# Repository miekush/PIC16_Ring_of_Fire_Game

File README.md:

# PIC16_Ring_of_Fire_Game
A PIC16 based LED Reaction Time Game

This is a simple LED reaction time game based on the classes light ring redemption games seen in arcades. 

# Project Description

The device uses a PIC16F15223 8-bit microcontroller to drive a ring of 1206 LEDs. A low cost tactile switch starts and stops the led chaser and allows for switching between game mode and a speed settings mode depending on the press duration. Programming the device is completed via the onboard Tag-Connect footprint.

# Breadboard Prototype

# Enclosure

To make the device more comfortable for handheld use, I designed a small enclosure which can be easily 3D printed for a more professional device appearence.

Designed by Mike Kushnerik (MKE) in KiCad V5

# License

MKE supports the open source hardware community by sharing hardware design files freely on GitHub!

Please support MKE by purchasing products on [Tindie](https://www.tindie.com/stores/mkengineering/)!

Designed by Mike Kushnerik for MKEngineering

Licensed under [Creative Commons Attribution-ShareAlike CC BY-SA 3.0](http://creativecommons.org/licenses/by-sa/3.0/)

All text above must be included in any redistribution!

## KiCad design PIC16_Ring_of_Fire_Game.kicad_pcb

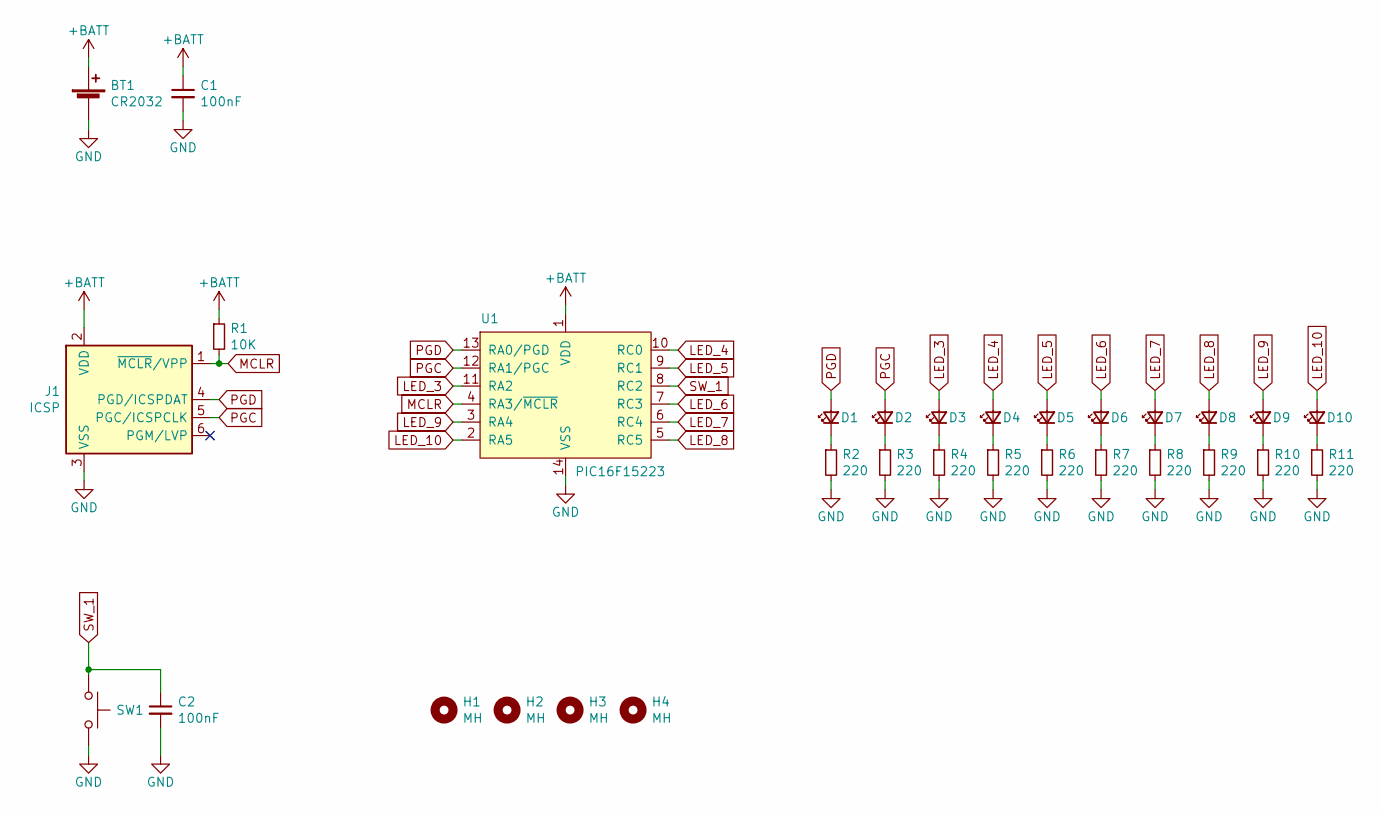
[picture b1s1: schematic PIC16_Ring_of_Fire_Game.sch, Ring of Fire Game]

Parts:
BT1: CR2032; 1060TR
C1, C2: 100nF; C_0603_1608Metric
D1, D2, D3, D4, D5, D6, D7, D8, D9, D10: 5mm LED; LED_1206_3216Metric
H1, H2, H3, H4: MH; MountingHole_3.2mm_M3
J1: ICSP; Tag-Connect_TC2030-IDC-NL_2x03_P1.27mm_Vertical
R1: 10K; R_0603_1608Metric
R2, R3, R4, R5, R6, R7, R8, R9, R10, R11: 220; R_0603_1608Metric
SW1: START/STOP; SW_SPST_PTS645
U1: PIC16F15223; SOIC-14_3.9x8.7mm_P1.27mm

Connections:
+BATT: BT1.1 (+), C1.1, J1.2 (VDD), R1.1, U1.1 (VDD)
GND: BT1.2 (-), C1.2, C2.2, J1.3 (VSS), R2.2, R3.2, R4.2, R5.2, R6.2, R7.2, R8.2, R9.2, R10.2, R11.2, SW1.1, U1.14 (VSS)
LED_3: D3.2 (A), U1.11 (RA2)
LED_4: D4.2 (A), U1.10 (RC0)
LED_5: D5.2 (A), U1.9 (RC1)
LED_6: D6.2 (A), U1.7 (RC3)
LED_7: D7.2 (A), U1.6 (RC4)
LED_8: D8.2 (A), U1.5 (RC5)
LED_9: D9.2 (A), U1.3 (RA4)
LED_10: D10.2 (A), U1.2 (RA5)
MCLR: J1.1 (~MCLR~/VPP), R1.2, U1.4 (RA3/~MCLR)
unnamed: D1.1 (K), R2.1
unnamed: D2.1 (K), R3.1
unnamed: D3.1 (K), R4.1
unnamed: D4.1 (K), R5.1
unnamed: D5.1 (K), R6.1
unnamed: D6.1 (K), R7.1
unnamed: D7.1 (K), R8.1
unnamed: D8.1 (K), R9.1
unnamed: D9.1 (K), R10.1
unnamed: D10.1 (K), R11.1
PGC: D2.2 (A), J1.5 (PGC/ICSPCLK), U1.12 (RA1/PGC)
PGD: D1.2 (A), J1.4 (PGD/ICSPDAT), U1.13 (RA0/PGD)
SW_1: C2.1, SW1.2, U1.8 (RC2)

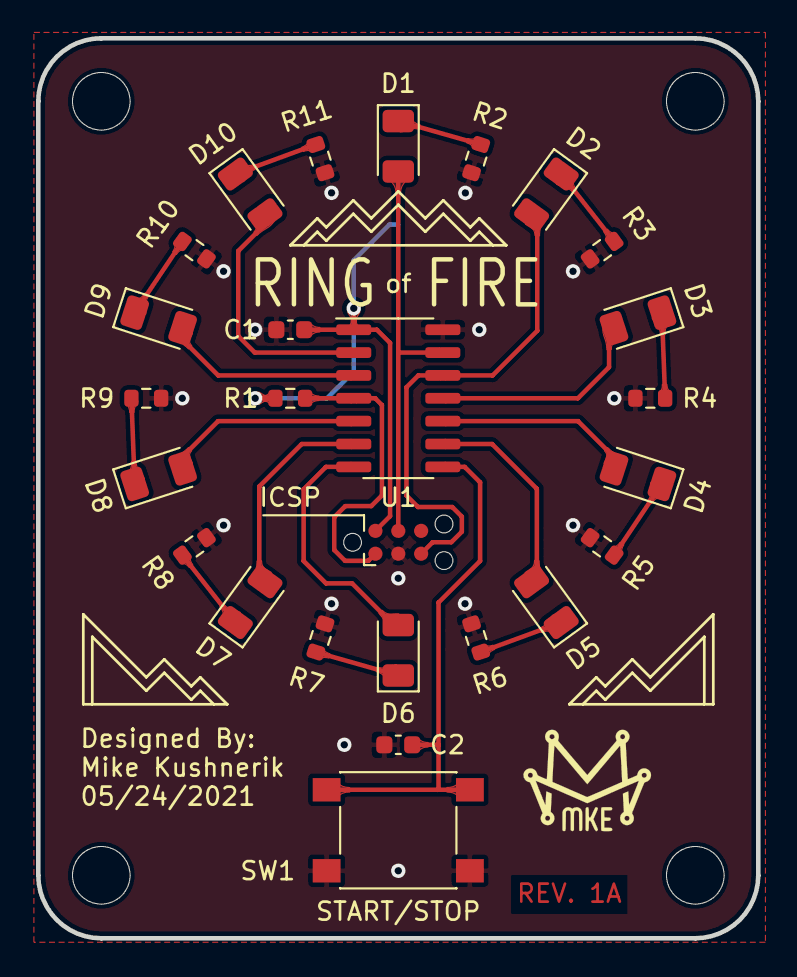
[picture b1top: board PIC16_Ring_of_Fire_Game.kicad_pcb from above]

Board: 2 copper layers, 40.0 x 50.0 mm, 31 parts (1 on the bottom side), 24 nets.

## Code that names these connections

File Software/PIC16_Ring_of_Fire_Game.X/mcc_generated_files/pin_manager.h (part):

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// get/set LED_1 aliases
#define LED_1_TRIS                 TRISAbits.TRISA0
#define LED_1_LAT                  LATAbits.LATA0
#define LED_1_PORT                 PORTAbits.RA0
#define LED_1_WPU                  WPUAbits.WPUA0
#define LED_1_OD                   ODCONAbits.ODCA0
#define LED_1_ANS                  ANSELAbits.ANSA0
#define LED_1_SetHigh()            do { LATAbits.LATA0 = 1; } while(0)
#define LED_1_SetLow()             do { LATAbits.LATA0 = 0; } while(0)
#define LED_1_Toggle()             do { LATAbits.LATA0 = ~LATAbits.LATA0; } while(0)
#define LED_1_GetValue()           PORTAbits.RA0
#define LED_1_SetDigitalInput()    do { TRISAbits.TRISA0 = 1; } while(0)
#define LED_1_SetDigitalOutput()   do { TRISAbits.TRISA0 = 0; } while(0)
#define LED_1_SetPullup()          do { WPUAbits.WPUA0 = 1; } while(0)
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// get/set LED_2 aliases
#define LED_2_TRIS                 TRISAbits.TRISA1
#define LED_2_LAT                  LATAbits.LATA1
#define LED_2_PORT                 PORTAbits.RA1
#define LED_2_WPU                  WPUAbits.WPUA1
#define LED_2_OD                   ODCONAbits.ODCA1
#define LED_2_ANS                  ANSELAbits.ANSA1
#define LED_2_SetHigh()            do { LATAbits.LATA1 = 1; } while(0)
#define LED_2_SetLow()             do { LATAbits.LATA1 = 0; } while(0)
#define LED_2_Toggle()             do { LATAbits.LATA1 = ~LATAbits.LATA1; } while(0)
#define LED_2_GetValue()           PORTAbits.RA1
#define LED_2_SetDigitalInput()    do { TRISAbits.TRISA1 = 1; } while(0)
#define LED_2_SetDigitalOutput()   do { TRISAbits.TRISA1 = 0; } while(0)
#define LED_2_SetPullup()          do { WPUAbits.WPUA1 = 1; } while(0)
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// get/set LED_3 aliases
#define LED_3_TRIS                 TRISAbits.TRISA2
#define LED_3_LAT                  LATAbits.LATA2
#define LED_3_PORT                 PORTAbits.RA2
#define LED_3_WPU                  WPUAbits.WPUA2
#define LED_3_OD                   ODCONAbits.ODCA2
#define LED_3_ANS                  ANSELAbits.ANSA2
#define LED_3_SetHigh()            do { LATAbits.LATA2 = 1; } while(0)
#define LED_3_SetLow()             do { LATAbits.LATA2 = 0; } while(0)
#define LED_3_Toggle()             do { LATAbits.LATA2 = ~LATAbits.LATA2; } while(0)
#define LED_3_GetValue()           PORTAbits.RA2
#define LED_3_SetDigitalInput()    do { TRISAbits.TRISA2 = 1; } while(0)
#define LED_3_SetDigitalOutput()   do { TRISAbits.TRISA2 = 0; } while(0)
#define LED_3_SetPullup()          do { WPUAbits.WPUA2 = 1; } while(0)
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// get/set LED_10 aliases
#define LED_10_TRIS                 TRISAbits.TRISA4
#define LED_10_LAT                  LATAbits.LATA4
#define LED_10_PORT                 PORTAbits.RA4
#define LED_10_WPU                  WPUAbits.WPUA4
#define LED_10_OD                   ODCONAbits.ODCA4
#define LED_10_ANS                  ANSELAbits.ANSA4
#define LED_10_SetHigh()            do { LATAbits.LATA4 = 1; } while(0)
#define LED_10_SetLow()             do { LATAbits.LATA4 = 0; } while(0)
#define LED_10_Toggle()             do { LATAbits.LATA4 = ~LATAbits.LATA4; } while(0)
#define LED_10_GetValue()           PORTAbits.RA4
#define LED_10_SetDigitalInput()    do { TRISAbits.TRISA4 = 1; } while(0)
#define LED_10_SetDigitalOutput()   do { TRISAbits.TRISA4 = 0; } while(0)
#define LED_10_SetPullup()          do { WPUAbits.WPUA4 = 1; } while(0)
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#define RA5_SetHigh()            do { LATAbits.LATA5 = 1; } while(0)
#define RA5_SetLow()             do { LATAbits.LATA5 = 0; } while(0)
#define RA5_Toggle()             do { LATAbits.LATA5 = ~LATAbits.LATA5; } while(0)
#define RA5_GetValue()              PORTAbits.RA5
#define RA5_SetDigitalInput()    do { TRISAbits.TRISA5 = 1; } while(0)
#define RA5_SetDigitalOutput()   do { TRISAbits.TRISA5 = 0; } while(0)
#define RA5_SetPullup()             do { WPUAbits.WPUA5 = 1; } while(0)
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// get/set LED_4 aliases
#define LED_4_TRIS                 TRISCbits.TRISC0
#define LED_4_LAT                  LATCbits.LATC0
#define LED_4_PORT                 PORTCbits.RC0
#define LED_4_WPU                  WPUCbits.WPUC0
#define LED_4_OD                   ODCONCbits.ODCC0
#define LED_4_ANS                  ANSELCbits.ANSC0
#define LED_4_SetHigh()            do { LATCbits.LATC0 = 1; } while(0)
#define LED_4_SetLow()             do { LATCbits.LATC0 = 0; } while(0)
#define LED_4_Toggle()             do { LATCbits.LATC0 = ~LATCbits.LATC0; } while(0)
#define LED_4_GetValue()           PORTCbits.RC0
#define LED_4_SetDigitalInput()    do { TRISCbits.TRISC0 = 1; } while(0)
#define LED_4_SetDigitalOutput()   do { TRISCbits.TRISC0 = 0; } while(0)
#define LED_4_SetPullup()          do { WPUCbits.WPUC0 = 1; } while(0)
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// get/set LED_5 aliases
#define LED_5_TRIS                 TRISCbits.TRISC1
#define LED_5_LAT                  LATCbits.LATC1
#define LED_5_PORT                 PORTCbits.RC1
#define LED_5_WPU                  WPUCbits.WPUC1
#define LED_5_OD                   ODCONCbits.ODCC1
#define LED_5_ANS                  ANSELCbits.ANSC1
#define LED_5_SetHigh()            do { LATCbits.LATC1 = 1; } while(0)
#define LED_5_SetLow()             do { LATCbits.LATC1 = 0; } while(0)
#define LED_5_Toggle()             do { LATCbits.LATC1 = ~LATCbits.LATC1; } while(0)
#define LED_5_GetValue()           PORTCbits.RC1
#define LED_5_SetDigitalInput()    do { TRISCbits.TRISC1 = 1; } while(0)
#define LED_5_SetDigitalOutput()   do { TRISCbits.TRISC1 = 0; } while(0)
#define LED_5_SetPullup()          do { WPUCbits.WPUC1 = 1; } while(0)
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// get/set LED_6 aliases
#define LED_6_TRIS                 TRISCbits.TRISC2
#define LED_6_LAT                  LATCbits.LATC2
#define LED_6_PORT                 PORTCbits.RC2
#define LED_6_WPU                  WPUCbits.WPUC2
#define LED_6_OD                   ODCONCbits.ODCC2
#define LED_6_ANS                  ANSELCbits.ANSC2
#define LED_6_SetHigh()            do { LATCbits.LATC2 = 1; } while(0)
#define LED_6_SetLow()             do { LATCbits.LATC2 = 0; } while(0)
#define LED_6_Toggle()             do { LATCbits.LATC2 = ~LATCbits.LATC2; } while(0)
#define LED_6_GetValue()           PORTCbits.RC2
#define LED_6_SetDigitalInput()    do { TRISCbits.TRISC2 = 1; } while(0)
#define LED_6_SetDigitalOutput()   do { TRISCbits.TRISC2 = 0; } while(0)
#define LED_6_SetPullup()          do { WPUCbits.WPUC2 = 1; } while(0)
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// get/set LED_7 aliases
#define LED_7_TRIS                 TRISCbits.TRISC3
#define LED_7_LAT                  LATCbits.LATC3
#define LED_7_PORT                 PORTCbits.RC3
#define LED_7_WPU                  WPUCbits.WPUC3
#define LED_7_OD                   ODCONCbits.ODCC3
#define LED_7_ANS                  ANSELCbits.ANSC3
#define LED_7_SetHigh()            do { LATCbits.LATC3 = 1; } while(0)
#define LED_7_SetLow()             do { LATCbits.LATC3 = 0; } while(0)
#define LED_7_Toggle()             do { LATCbits.LATC3 = ~LATCbits.LATC3; } while(0)
#define LED_7_GetValue()           PORTCbits.RC3
#define LED_7_SetDigitalInput()    do { TRISCbits.TRISC3 = 1; } while(0)
#define LED_7_SetDigitalOutput()   do { TRISCbits.TRISC3 = 0; } while(0)
#define LED_7_SetPullup()          do { WPUCbits.WPUC3 = 1; } while(0)
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// get/set LED_8 aliases
#define LED_8_TRIS                 TRISCbits.TRISC4
#define LED_8_LAT                  LATCbits.LATC4
#define LED_8_PORT                 PORTCbits.RC4
#define LED_8_WPU                  WPUCbits.WPUC4
#define LED_8_OD                   ODCONCbits.ODCC4
#define LED_8_ANS                  ANSELCbits.ANSC4
#define LED_8_SetHigh()            do { LATCbits.LATC4 = 1; } while(0)
#define LED_8_SetLow()             do { LATCbits.LATC4 = 0; } while(0)
#define LED_8_Toggle()             do { LATCbits.LATC4 = ~LATCbits.LATC4; } while(0)
#define LED_8_GetValue()           PORTCbits.RC4
#define LED_8_SetDigitalInput()    do { TRISCbits.TRISC4 = 1; } while(0)
#define LED_8_SetDigitalOutput()   do { TRISCbits.TRISC4 = 0; } while(0)
#define LED_8_SetPullup()          do { WPUCbits.WPUC4 = 1; } while(0)
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// get/set LED_9 aliases
#define LED_9_TRIS                 TRISCbits.TRISC5
#define LED_9_LAT                  LATCbits.LATC5
#define LED_9_PORT                 PORTCbits.RC5
#define LED_9_WPU                  WPUCbits.WPUC5
#define LED_9_OD                   ODCONCbits.ODCC5
#define LED_9_ANS                  ANSELCbits.ANSC5
#define LED_9_SetHigh()            do { LATCbits.LATC5 = 1; } while(0)
#define LED_9_SetLow()             do { LATCbits.LATC5 = 0; } while(0)
#define LED_9_Toggle()             do { LATCbits.LATC5 = ~LATCbits.LATC5; } while(0)
#define LED_9_GetValue()           PORTCbits.RC5
#define LED_9_SetDigitalInput()    do { TRISCbits.TRISC5 = 1; } while(0)
#define LED_9_SetDigitalOutput()   do { TRISCbits.TRISC5 = 0; } while(0)
#define LED_9_SetPullup()          do { WPUCbits.WPUC5 = 1; } while(0)
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
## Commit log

2021-05-28 Initial Upload
2021-06-02 Update LED pins to match PCB

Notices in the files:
Software/PIC16_Ring_of_Fire_Game.X/mcc_generated_files/pin_manager.h:
(c) 2018 Microchip Technology Inc. and its subsidiaries.
